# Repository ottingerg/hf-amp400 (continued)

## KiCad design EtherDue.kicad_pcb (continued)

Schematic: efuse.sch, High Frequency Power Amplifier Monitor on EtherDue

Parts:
C1301, C1702, C1704: 100n/X7R; C_0603
C1705, C1706: 10n/X7R; C_0603
C1707, C1708: 1n/X7R; C_0805
C1709: DNP; C_0603
C1710: 1n/X7R; C_0603
JP1701: JUMPER3; Pin_Header_Straight_1x03
L1701: WE-CBF-742792093; R_0805
LED1701: RED; LED-0805
Q1701, Q1702: BSS123; sot23-gsd
Q1703, Q1704: BSS308; sot23-gsd
R1301: 10k; R_0603
R1302, R1703, R1707: 100R; R_0603
R1307: 2k2; R_0805
R1702, R1706: 4k7; R_0603
R1704: 1k; R_0805
R1708, R1709: 0R; R_0603
R1711: 91k; R_0603
R1712: 4k7; 0603
SW1301: SW_PUSH; SW_TACTILE_SMD
U1701: MCP6H04; SOIC-14_3.9x8.7mm_Pitch1.27mm
U1702: INA206; SOIC-14_3.9x8.7mm_Pitch1.27mm
U1703: MEU1S1212ZC; MEU1-Murata-DCDC
VR1701: 10k; Potentiometer_Bourns_3296W_3-8Zoll_Inline_ScrewUp

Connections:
/eFuse 1 (10A)/+Shunt: R1708.2; also elsewhere on the board
/eFuse 1 (10A)/-Shunt: R1709.2; also elsewhere on the board
/eFuse 1 (10A)/Comp+: U1702.2 (OUT), U1702.4 (CMP1_IN+); also elsewhere on the board
/eFuse 1 (10A)/Gate: C1707.1, C1710.1, U1703.4 (VOUT+); also elsewhere on the board
/eFuse 1 (10A)/LED_K: LED1701.K, R1704.2; also elsewhere on the board
/eFuse 1 (10A)/Source: C1708.1, C1710.2, U1703.3 (VOUT-); also elsewhere on the board
unnamed: C1705.1, C1709.1, R1708.1, U1702.14 (VIN+)
unnamed: C1706.1, C1709.2, R1709.1, U1702.13 (VIN-)
unnamed: C1707.2, L1701.1, U1703.2 (VIN+)
unnamed 266: JP1701.2; also elsewhere on the board
unnamed: L1701.2, Q1704.D
unnamed: Q1701.D, R1704.1
unnamed: Q1701.G, R1703.1
unnamed: Q1702.D, Q1704.G, R1706.1
unnamed 301: Q1702.G; also elsewhere on the board
unnamed: Q1703.D, Q1704.S
unnamed: Q1703.G, R1707.2
unnamed: R1702.2, U1702.5 (CMP2_IN-)
unnamed: R1703.2, R1707.1, R1712.2, U1702.11 (CMP1_OUT)
unnamed: R1711.1, VR1701.3
unnamed: U1701.1, U1701.2 (-), U1702.3 (CMP1_IN-/0.6V_REF)
PIN24: JP1701.3; also elsewhere on the board

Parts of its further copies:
C1302, C1401, C1402, C1701, C1801, C1802, C1804, C1901, C1902, C1904: 100n/X7R; C_0603
C1805, C1806, C1905, C1906: 10n/X7R; C_0603
C1807, C1808, C1907, C1908: 1n/X7R; C_0805
C1809, C1909: DNP; C_0603
C1810, C1910: 1n/X7R; C_0603
JP1301, JP1401, JP1801, JP1901: JUMPER3; Pin_Header_Straight_1x03
L1801, L1901: WE-CBF-742792093; R_0805
LED1301, LED1401, LED1801, LED1901: RED; LED-0805
Q1301, Q1304, Q1401, Q1404, Q1801, Q1802, Q1901, Q1902: BSS123; sot23-gsd
Q1302, Q1303, Q1402, Q1403, Q1803, Q1804, Q1903, Q1904: BSS308; sot23-gsd
R1306, R1406, R1808, R1809, R1908, R1909: 0R; R_0603
R1308, R1402, R1408, R1705, R1803, R1805, R1807, R1903, R1905, R1907: 100R; R_0603
R1309, R1409, R1804, R1904: 1k; R_0805
R1407, R1710, R1810, R1910: 2k2; R_0805
R1701, R1801, R1901: 10k; R_0603
R1802, R1806, R1902, R1906: 4k7; R_0603
R1811, R1911: 91k; R_0603
R1812, R1912: 4k7; 0603
SW1401, SW1701, SW1801, SW1901: SW_PUSH; SW_TACTILE_SMD
U1403, U1802, U1902: MEU1S1212ZC; MEU1-Murata-DCDC
U1801, U1901: INA206; SOIC-14_3.9x8.7mm_Pitch1.27mm
VR1801, VR1901: 10k; Potentiometer_Bourns_3296W_3-8Zoll_Inline_ScrewUp

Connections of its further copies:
/Analog I/O/VIN1: R1306.2; also elsewhere on the board
/Analog I/O/VIN3: R1406.2; also elsewhere on the board
/eFuse 1 (10A)/Gate: R1710.2; also elsewhere on the board
/eFuse 1 (10A)/Source: R1710.1; also elsewhere on the board
/eFuse 2 (10A)/+Shunt: R1808.2; also elsewhere on the board
/eFuse 2 (10A)/-Shunt: R1809.2; also elsewhere on the board
/eFuse 2 (10A)/Comp+: U1801.2 (OUT), U1801.4 (CMP1_IN+); also elsewhere on the board
/eFuse 2 (10A)/Gate: C1807.1, C1810.1, R1810.2, U1802.4 (VOUT+); also elsewhere on the board
/eFuse 2 (10A)/LED_K: LED1801.K, R1804.2; also elsewhere on the board
/eFuse 2 (10A)/Reset\: R1801.2, SW1801.2, U1801.8 (CMP1_RESET\); also elsewhere on the board
/eFuse 2 (10A)/Source: C1808.1, C1810.2, R1810.1, U1802.3 (VOUT-); also elsewhere on the board
/eFuse 3 (60A)/+Shunt: R1908.2; also elsewhere on the board
/eFuse 3 (60A)/-Shunt: R1909.2; also elsewhere on the board
/eFuse 3 (60A)/Comp+: U1901.4 (CMP1_IN+); also elsewhere on the board
/eFuse 3 (60A)/Gate: C1907.1, C1910.1, R1910.2, U1902.4 (VOUT+); also elsewhere on the board
/eFuse 3 (60A)/ISense: U1901.2 (OUT); also elsewhere on the board
/eFuse 3 (60A)/LED_K: LED1901.K, R1904.2; also elsewhere on the board
/eFuse 3 (60A)/Reset\: R1901.2, SW1901.2, U1901.8 (CMP1_RESET\); also elsewhere on the board
/eFuse 3 (60A)/Source: C1908.1, C1910.2, R1910.1, U1902.3 (VOUT-); also elsewhere on the board
unnamed 184: R1306.1; also elsewhere on the board
unnamed 185: C1401.1, C1402.1; also elsewhere on the board
unnamed 192: R1406.1; also elsewhere on the board
unnamed 200: C1801.1, VR1801.2; also elsewhere on the board
unnamed: C1805.1, C1809.1, R1808.1, U1801.14 (VIN+)
unnamed: C1806.1, C1809.2, R1809.1, U1801.13 (VIN-)
unnamed: C1807.2, L1801.1, U1802.2 (VIN+)
unnamed 204: C1901.1, VR1901.2; also elsewhere on the board
unnamed: C1905.1, C1909.1, R1908.1, U1901.14 (VIN+)
unnamed: C1906.1, C1909.2, R1909.1, U1901.13 (VIN-)
unnamed: C1907.2, L1901.1, U1902.2 (VIN+)
unnamed 266: R1705.1; also elsewhere on the board
unnamed: JP1801.2, R1805.1
unnamed: JP1901.2, R1905.1
unnamed: L1801.2, Q1804.D
unnamed: L1901.2, Q1904.D
unnamed 301: R1705.2; also elsewhere on the board
unnamed: Q1801.D, R1804.1
unnamed: Q1801.G, R1803.1
unnamed: Q1802.D, Q1804.G, R1806.1
unnamed: Q1802.G, R1805.2
unnamed: Q1803.D, Q1804.S
unnamed: Q1803.G, R1807.2
unnamed: Q1901.D, R1904.1
unnamed: Q1901.G, R1903.1
unnamed: Q1902.D, Q1904.G, R1906.1
unnamed: Q1902.G, R1905.2
unnamed: Q1903.D, Q1904.S
unnamed: Q1903.G, R1907.2
unnamed: R1802.2, U1801.5 (CMP2_IN-)
unnamed: R1803.2, R1807.1, R1812.2, U1801.11 (CMP1_OUT)
unnamed: R1811.1, VR1801.3
unnamed: R1902.2, U1901.5 (CMP2_IN-)
unnamed: R1903.2, R1907.1, R1912.2, U1901.11 (CMP1_OUT)
unnamed: R1911.1, VR1901.3
unnamed 367: U1801.3 (CMP1_IN-/0.6V_REF); also elsewhere on the board
unnamed 368: U1901.3 (CMP1_IN-/0.6V_REF); also elsewhere on the board
PIN24: JP1801.3, JP1901.3; also elsewhere on the board

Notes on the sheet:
12V/12V
10-turn potentiometer
Decoupling C is on parent sheet

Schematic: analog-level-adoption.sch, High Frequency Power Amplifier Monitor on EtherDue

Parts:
C2001, C2002, C2003, C2010, C2011, C2012: 10n/X7R; C_0603
C2004, C2005, C2006, C2007, C2008, C2009, C2013, C2014: 1n/X7R; C_0603
D2001, D2002, D2003, D2004: BAT54S; sot23
R2001, R2002, R2003: 47k; R_0805
R2004, R2005, R2006: 2k7; R_0603
R2007, R2008, R2009: 10k; R_0603
R2010, R2011: DNP; R_0603
R2012: 6k8; R_0603

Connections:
/Analog I/O/+3V3: C2004.1, C2006.1, C2008.1, C2013.1, D2001.3 (cathode), D2002.3 (cathode), D2003.3 (cathode), D2004.3 (cathode); also elsewhere on the board
/Analog Level Adoption/I_Fuse1_Out: C2010.1, R2007.2, R2010.2; also elsewhere on the board
/Analog Level Adoption/I_Fuse2_Out: C2011.1, R2008.2, R2011.2; also elsewhere on the board
/eFuse 1 (10A)/Comp+: R2007.1; also elsewhere on the board
/eFuse 1 (10A)/Source: R2001.1; also elsewhere on the board
/eFuse 2 (10A)/Comp+: R2008.1; also elsewhere on the board
/eFuse 2 (10A)/Source: R2002.1; also elsewhere on the board
/eFuse 3 (60A)/ISense: R2009.1; also elsewhere on the board
/eFuse 3 (60A)/Source: R2003.1; also elsewhere on the board
AD2: C2001.1, C2004.2, C2005.1, D2001.2 (AK), R2001.2, R2004.2; also elsewhere on the board
AD3: C2002.1, C2006.2, C2007.1, D2002.2 (AK), R2002.2, R2005.2; also elsewhere on the board
AD4: C2003.1, C2008.2, C2009.1, D2003.2 (AK), R2003.2, R2006.2; also elsewhere on the board
AD5: C2012.1, C2013.2, C2014.1, D2004.2 (AK), R2009.2, R2012.2; also elsewhere on the board

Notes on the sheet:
Voltages from 60V to 3.3V
Currents of F1 and F2 from 12V to 5V and of F3 from 12V to 3.3V
0...5V
0...3.3V
0...60V
0...12V
place this 1nF near ADC
to VIN0
to VIN2

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
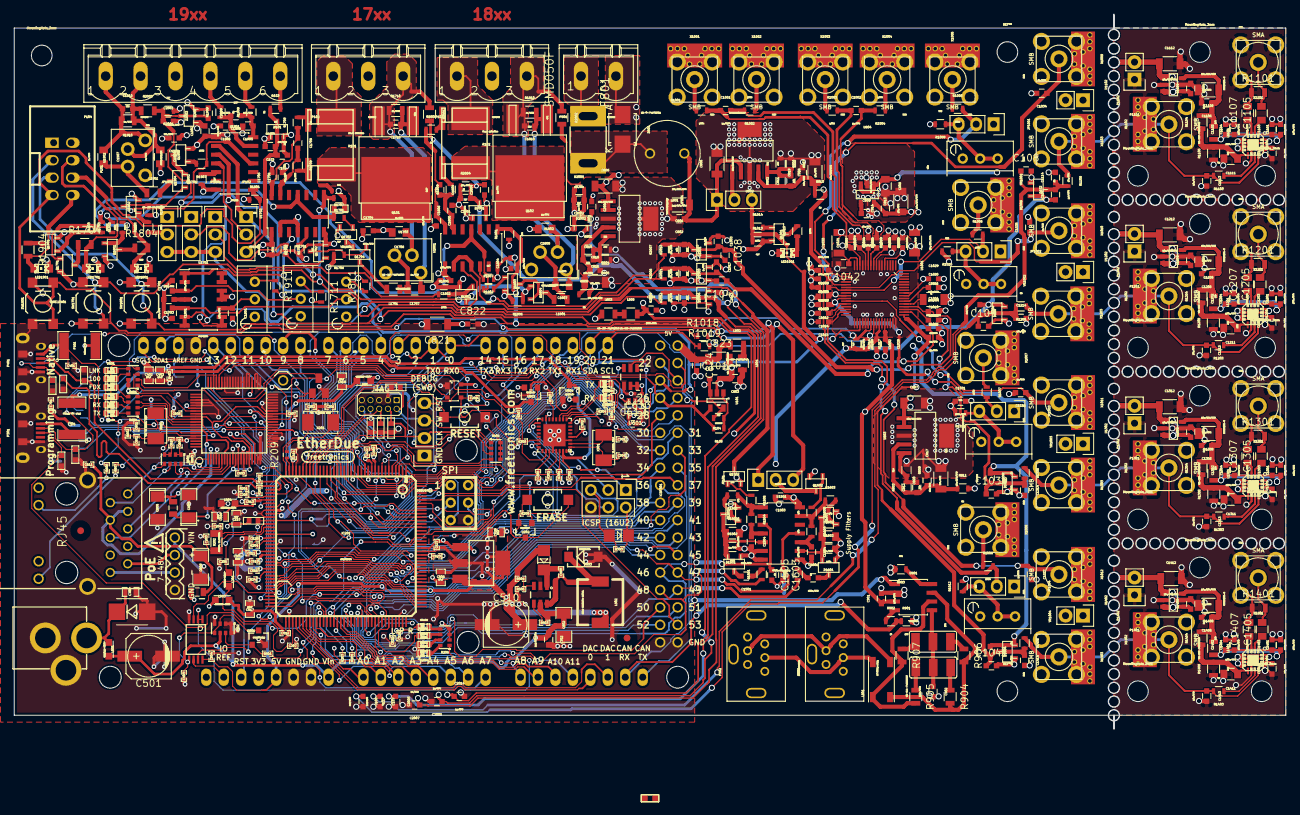
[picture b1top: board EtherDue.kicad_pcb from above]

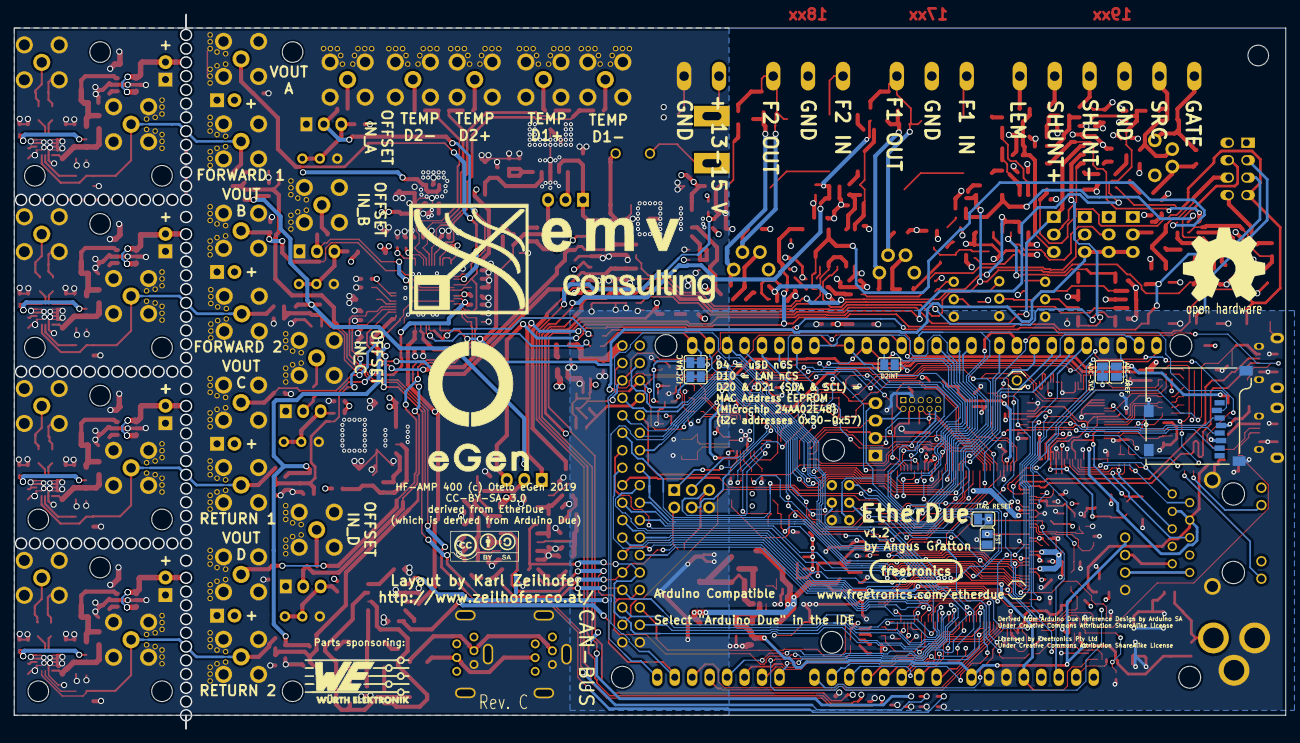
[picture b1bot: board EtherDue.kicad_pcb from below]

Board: 4 copper layers, 185.0 x 104.0 mm, 620 parts (9 on the bottom side), 377 nets.

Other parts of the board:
FIDUCIAL: val**; FIDUCIAL
FIDUCIAL#2: val**; FIDUCIAL
LOGO_FREETRONICS: val**; LOGO_FREETRONICS
LOGO_FREETRONICS_SMALL: val**; LOGO_FREETRONICS_SMALL
MountingHole_3mm, MountingHole_3mm#2, MountingHole_3mm#3, MountingHole_3mm#4, MountingHole_3mm#5, MountingHole_3mm#6, MountingHole_3mm#7, MountingHole_3mm#8, MountingHole_3mm#9, MountingHole_3mm#10, MountingHole_3mm#11, MountingHole_3mm#12, MountingHole_3mm#13: VAL**; MountingHole_3mm

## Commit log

2015-07-03 first produced pcb 20150617
2015-07-03 adjusted Readme
2015-07-03 modified readme
2015-07-28 20150728
2015-10-06 fixed missing Rs before Potis - fixed (removed) AD7294 Vpp connection
2015-10-08 Rev B. Layout - Gerber/BOM need to be reexported
2017-12-06 Jumper documentation
2019-12-25 RevC
2019-12-25 RevC - gerber needs reexporting
2021-11-10 Update README.md
    https://forum.kicad.info/t/warning-avoid-all-links-to-kicad-pcb-org-use-kicad-org/31521
